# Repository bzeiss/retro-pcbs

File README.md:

# retro-pcbs
This site contains some stuff I have built for old retro computers.

I tinker with electronics, release stuff when I feel like it and I make it public when it's maybe not perfect. I'm not an electronics expert, so I may not always know what I'm doing. I learn the necessary electronics as I use it. Use at your own risk.

Be smart. Don't just trust the stuff I offer for download here. Take a look at schematics and PCB designs beforehand ;-)

Feedback is always very welcome 😄 Feel free to ask question in the [discussions](https://github.com/bzeiss/retro-pcbs/discussions).

***

The main content of this site (descriptions, documentations) can be found **[in the Wiki](https://github.com/bzeiss/retro-pcbs/wiki)**.

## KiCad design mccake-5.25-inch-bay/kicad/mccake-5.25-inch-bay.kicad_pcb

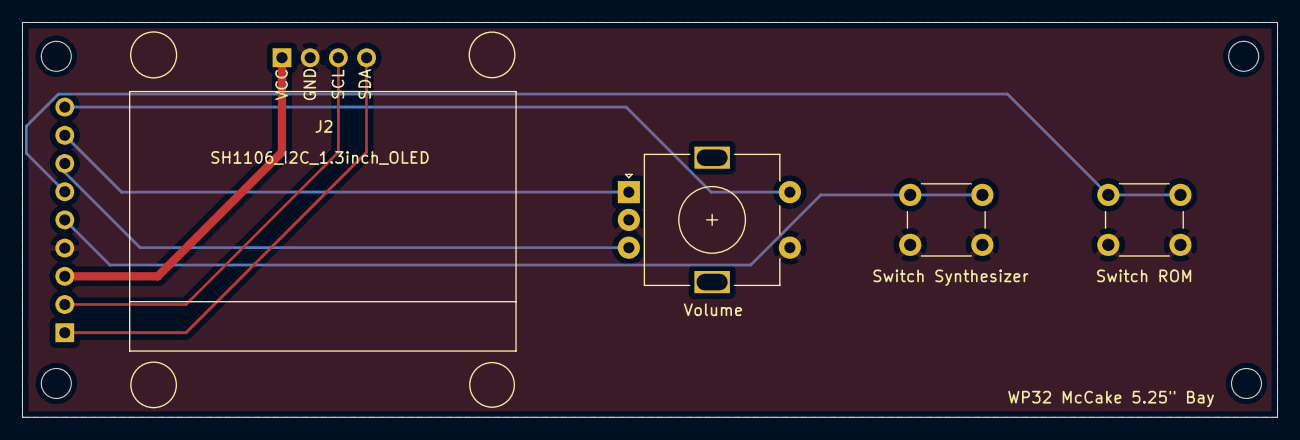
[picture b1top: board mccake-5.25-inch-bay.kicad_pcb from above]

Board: 2 copper layers, 113.0 x 35.6 mm, 5 parts (1 on the bottom side), 9 nets.

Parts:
J1: McCakeConn_01x09; McCake_Pin_Breakout_1x09_P2.54mm_Vertical
J2: SH1106_I2C_1.3inch_OLED; SH1106_1.3_OLED
Switch ROM: SW_Push; SW_PUSH_6mm
Switch Synthesizer: SW_Push; SW_PUSH_6mm
Volume: Rotary_Encoder_Switch; RotaryEncoder_Alps_EC11E-Switch_Vertical_H20mm

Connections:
+3V3: J1.3.3V, J2.VCC
/B1: J1.B1, Switch Synthesizer.1
/B2: J1.B2, Switch ROM.1
/B3_CLK: J1.B3, Volume.B
/B4_DAT: J1.B4, Volume.A
/ENC_SW: J1.ENC, Volume.S2
/SCL: J1.SCL, J2.SCL
/SDA: J1.SDA, J2.SDA
GND: J1.GND, J2.GND, Switch ROM.2, Switch Synthesizer.2, Volume.C, Volume.S1

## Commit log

2021-06-29 initial commit of the mccake 5.25" bay
2021-07-03 added gerber
2021-07-04 3d models
